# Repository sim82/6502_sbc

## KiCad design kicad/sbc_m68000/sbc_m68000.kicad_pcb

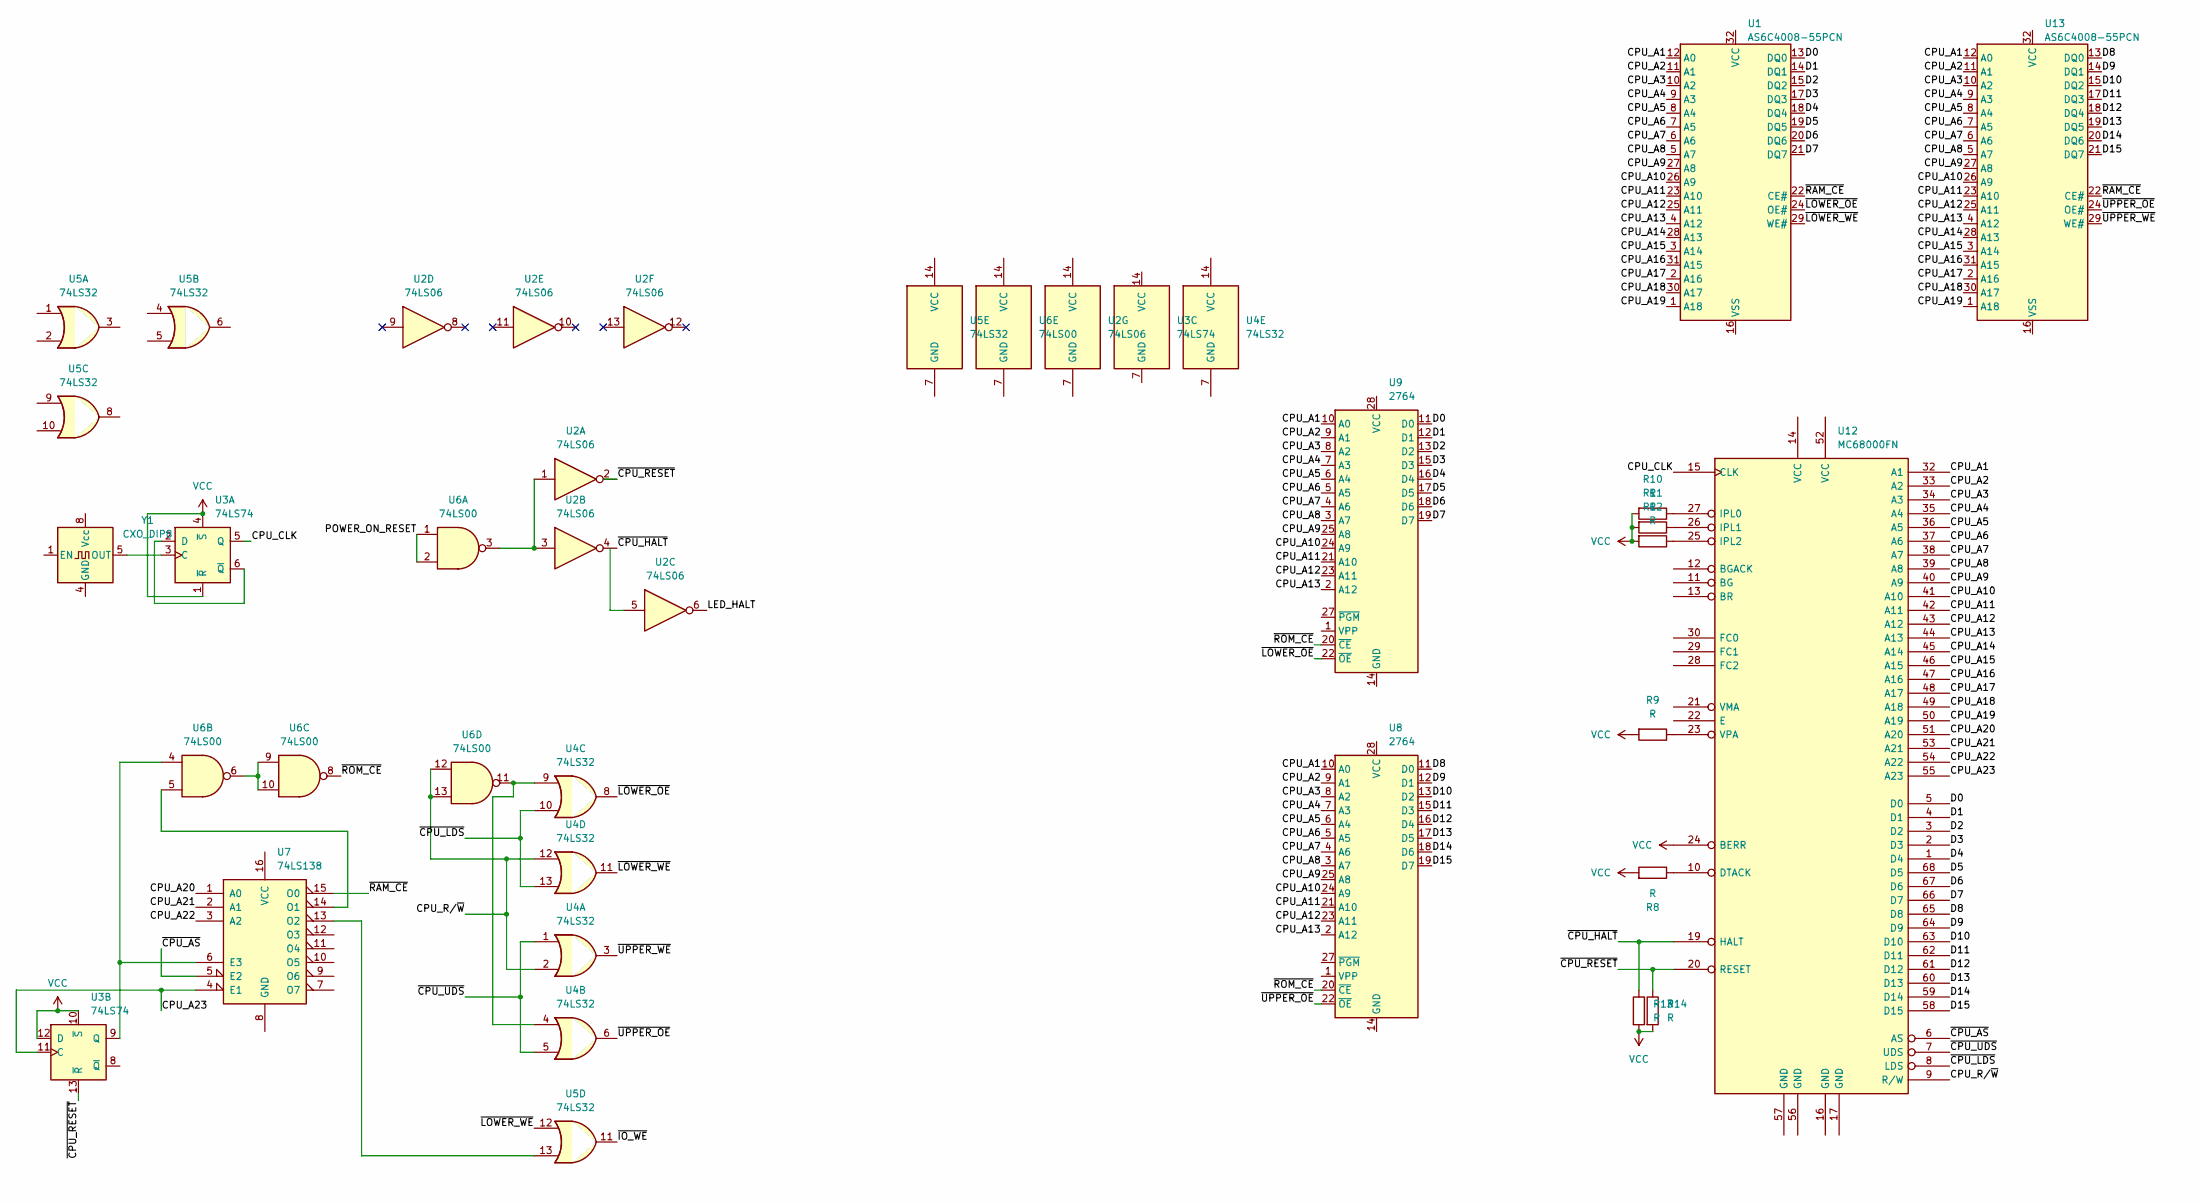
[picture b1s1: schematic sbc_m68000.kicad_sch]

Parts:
R8, R9, R10, R11, R12, R13, R14: R; R_0805_2012Metric_Pad1.20x1.40mm_HandSolder
U1, U13: AS6C4008-55PCN; TSOP-II-32_21.0x10.2mm_P1.27mm
U2: 74LS06; SO-14_3.9x8.65mm_P1.27mm
U3: 74LS74; SO-14_3.9x8.65mm_P1.27mm
U4, U5: 74LS32; SO-14_3.9x8.65mm_P1.27mm
U6: 74LS00; SO-14_3.9x8.65mm_P1.27mm
U7: 74LS138; SO-16_3.9x9.9mm_P1.27mm
U8, U9: 2764; DIP-28_W15.24mm_Socket
U12: MC68000FN; PLCC-68
Y1: CXO_DIP8; Oscillator_DIP-8

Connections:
/CPU_A1: U1.12 (A0), U8.10 (A0), U9.10 (A0), U12.32 (A1), U13.12 (A0)
/CPU_A2: U1.11 (A1), U8.9 (A1), U9.9 (A1), U12.33 (A2), U13.11 (A1)
/CPU_A3: U1.10 (A2), U8.8 (A2), U9.8 (A2), U12.34 (A3), U13.10 (A2)
/CPU_A4: U1.9 (A3), U8.7 (A3), U9.7 (A3), U12.35 (A4), U13.9 (A3)
/CPU_A5: U1.8 (A4), U8.6 (A4), U9.6 (A4), U12.36 (A5), U13.8 (A4)
/CPU_A6: U1.7 (A5), U8.5 (A5), U9.5 (A5), U12.37 (A6), U13.7 (A5)
/CPU_A7: U1.6 (A6), U8.4 (A6), U9.4 (A6), U12.38 (A7), U13.6 (A6)
/CPU_A8: U1.5 (A7), U8.3 (A7), U9.3 (A7), U12.39 (A8), U13.5 (A7)
/CPU_A9: U1.27 (A8), U8.25 (A8), U9.25 (A8), U12.40 (A9), U13.27 (A8)
/CPU_A10: U1.26 (A9), U8.24 (A9), U9.24 (A9), U12.41 (A10), U13.26 (A9)
/CPU_A11: U1.23 (A10), U8.21 (A10), U9.21 (A10), U12.42 (A11), U13.23 (A10)
/CPU_A12: U1.25 (A11), U8.23 (A11), U9.23 (A11), U12.43 (A12), U13.25 (A11)
/CPU_A13: U1.4 (A12), U8.2 (A12), U9.2 (A12), U12.44 (A13), U13.4 (A12)
/CPU_A14: U1.28 (A13), U12.45 (A14), U13.28 (A13)
/CPU_A15: U1.3 (A14), U12.46 (A15), U13.3 (A14)
/CPU_A16: U1.31 (A15), U12.47 (A16), U13.31 (A15)
/CPU_A17: U1.2 (A16), U12.48 (A17), U13.2 (A16)
/CPU_A18: U1.30 (A17), U12.49 (A18), U13.30 (A17)
/CPU_A19: U1.1 (A18), U12.50 (A19), U13.1 (A18)
/CPU_A20: U7.1 (A0), U12.51 (A20)
/CPU_A21: U7.2 (A1), U12.53 (A21)
/CPU_A22: U7.3 (A2), U12.54 (A22)
/CPU_A23: U3.11 (C), U7.4 (E1), U12.55 (A23)
/CPU_CLK: U3.5 (Q), U12.15 (CLK)
/CPU_R/~W: U4.2, U4.12, U6.12, U6.13, U12.9 (R/W)
/D0: U1.13 (DQ0), U9.11 (D0), U12.5 (D0)
/D1: U1.14 (DQ1), U9.12 (D1), U12.4 (D1)
/D2: U1.15 (DQ2), U9.13 (D2), U12.3 (D2)
/D3: U1.17 (DQ3), U9.15 (D3), U12.2 (D3)
/D4: U1.18 (DQ4), U9.16 (D4), U12.1 (D4)
/D5: U1.19 (DQ5), U9.17 (D5), U12.68 (D5)
/D6: U1.20 (DQ6), U9.18 (D6), U12.67 (D6)
/D7: U1.21 (DQ7), U9.19 (D7), U12.66 (D7)
/D8: U8.11 (D0), U12.65 (D8), U13.13 (DQ0)
/D9: U8.12 (D1), U12.64 (D9), U13.14 (DQ1)
/D10: U8.13 (D2), U12.63 (D10), U13.15 (DQ2)
/D11: U8.15 (D3), U12.62 (D11), U13.17 (DQ3)
/D12: U8.16 (D4), U12.61 (D12), U13.18 (DQ4)
/D13: U8.17 (D5), U12.60 (D13), U13.19 (DQ5)
/D14: U8.18 (D6), U12.59 (D14), U13.20 (DQ6)
/D15: U8.19 (D7), U12.58 (D15), U13.21 (DQ7)
/LED_HALT: U2.6
/POWER_ON_RESET: U6.1, U6.2
/~CPU_AS: U7.5 (E2), U12.6 (AS)
/~CPU_HALT: R13.1, U2.4, U12.19 (HALT)
/~CPU_LDS: U4.10, U4.13, U12.8 (LDS)
/~CPU_RESET: R14.1, U2.2, U3.13 (~R), U12.20 (RESET)
/~CPU_UDS: U4.1, U4.5, U12.7 (UDS)
/~IO_WE: U5.11
/~LOWER_OE: U1.24 (OE#), U4.8, U9.22 (~OE)
/~LOWER_WE: U1.29 (WE#), U4.11, U5.12
/~RAM_CE: U1.22 (CE#), U7.15 (O0), U13.22 (CE#)
/~ROM_CE: U6.8, U8.20 (~CE), U9.20 (~CE)
/~UPPER_OE: U4.6, U8.22 (~OE), U13.24 (OE#)
/~UPPER_WE: U4.3, U13.29 (WE#)
unnamed: U2.1, U2.3, U6.3
unnamed: U3.3 (C), Y1.5 (OUT)
unnamed: U3.2 (D), U3.6 (~Q)
unnamed: U3.9 (Q), U6.4, U7.6 (E3)
unnamed: U4.4, U4.9, U6.11
unnamed: U6.6, U6.9, U6.10
unnamed: U6.5, U7.14 (O1)
unnamed: U5.13, U7.13 (O2)
unnamed: R8.1, U12.10 (DTACK)
unnamed: R10.1, U12.27 (IPL0)
unnamed: R11.1, U12.26 (IPL1)
unnamed: R12.1, U12.25 (IPL2)
unnamed: R9.1, U12.23 (VPA)
VCC: R8.2, R9.2, R10.2, R11.2, R12.2, R13.2, R14.2, U3.1 (~R), U3.4 (~S), U3.10 (~S), U3.12 (D), U12.24 (BERR)

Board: 4 copper layers, 19 parts (0 on the bottom side), 67 nets, no tracks yet.

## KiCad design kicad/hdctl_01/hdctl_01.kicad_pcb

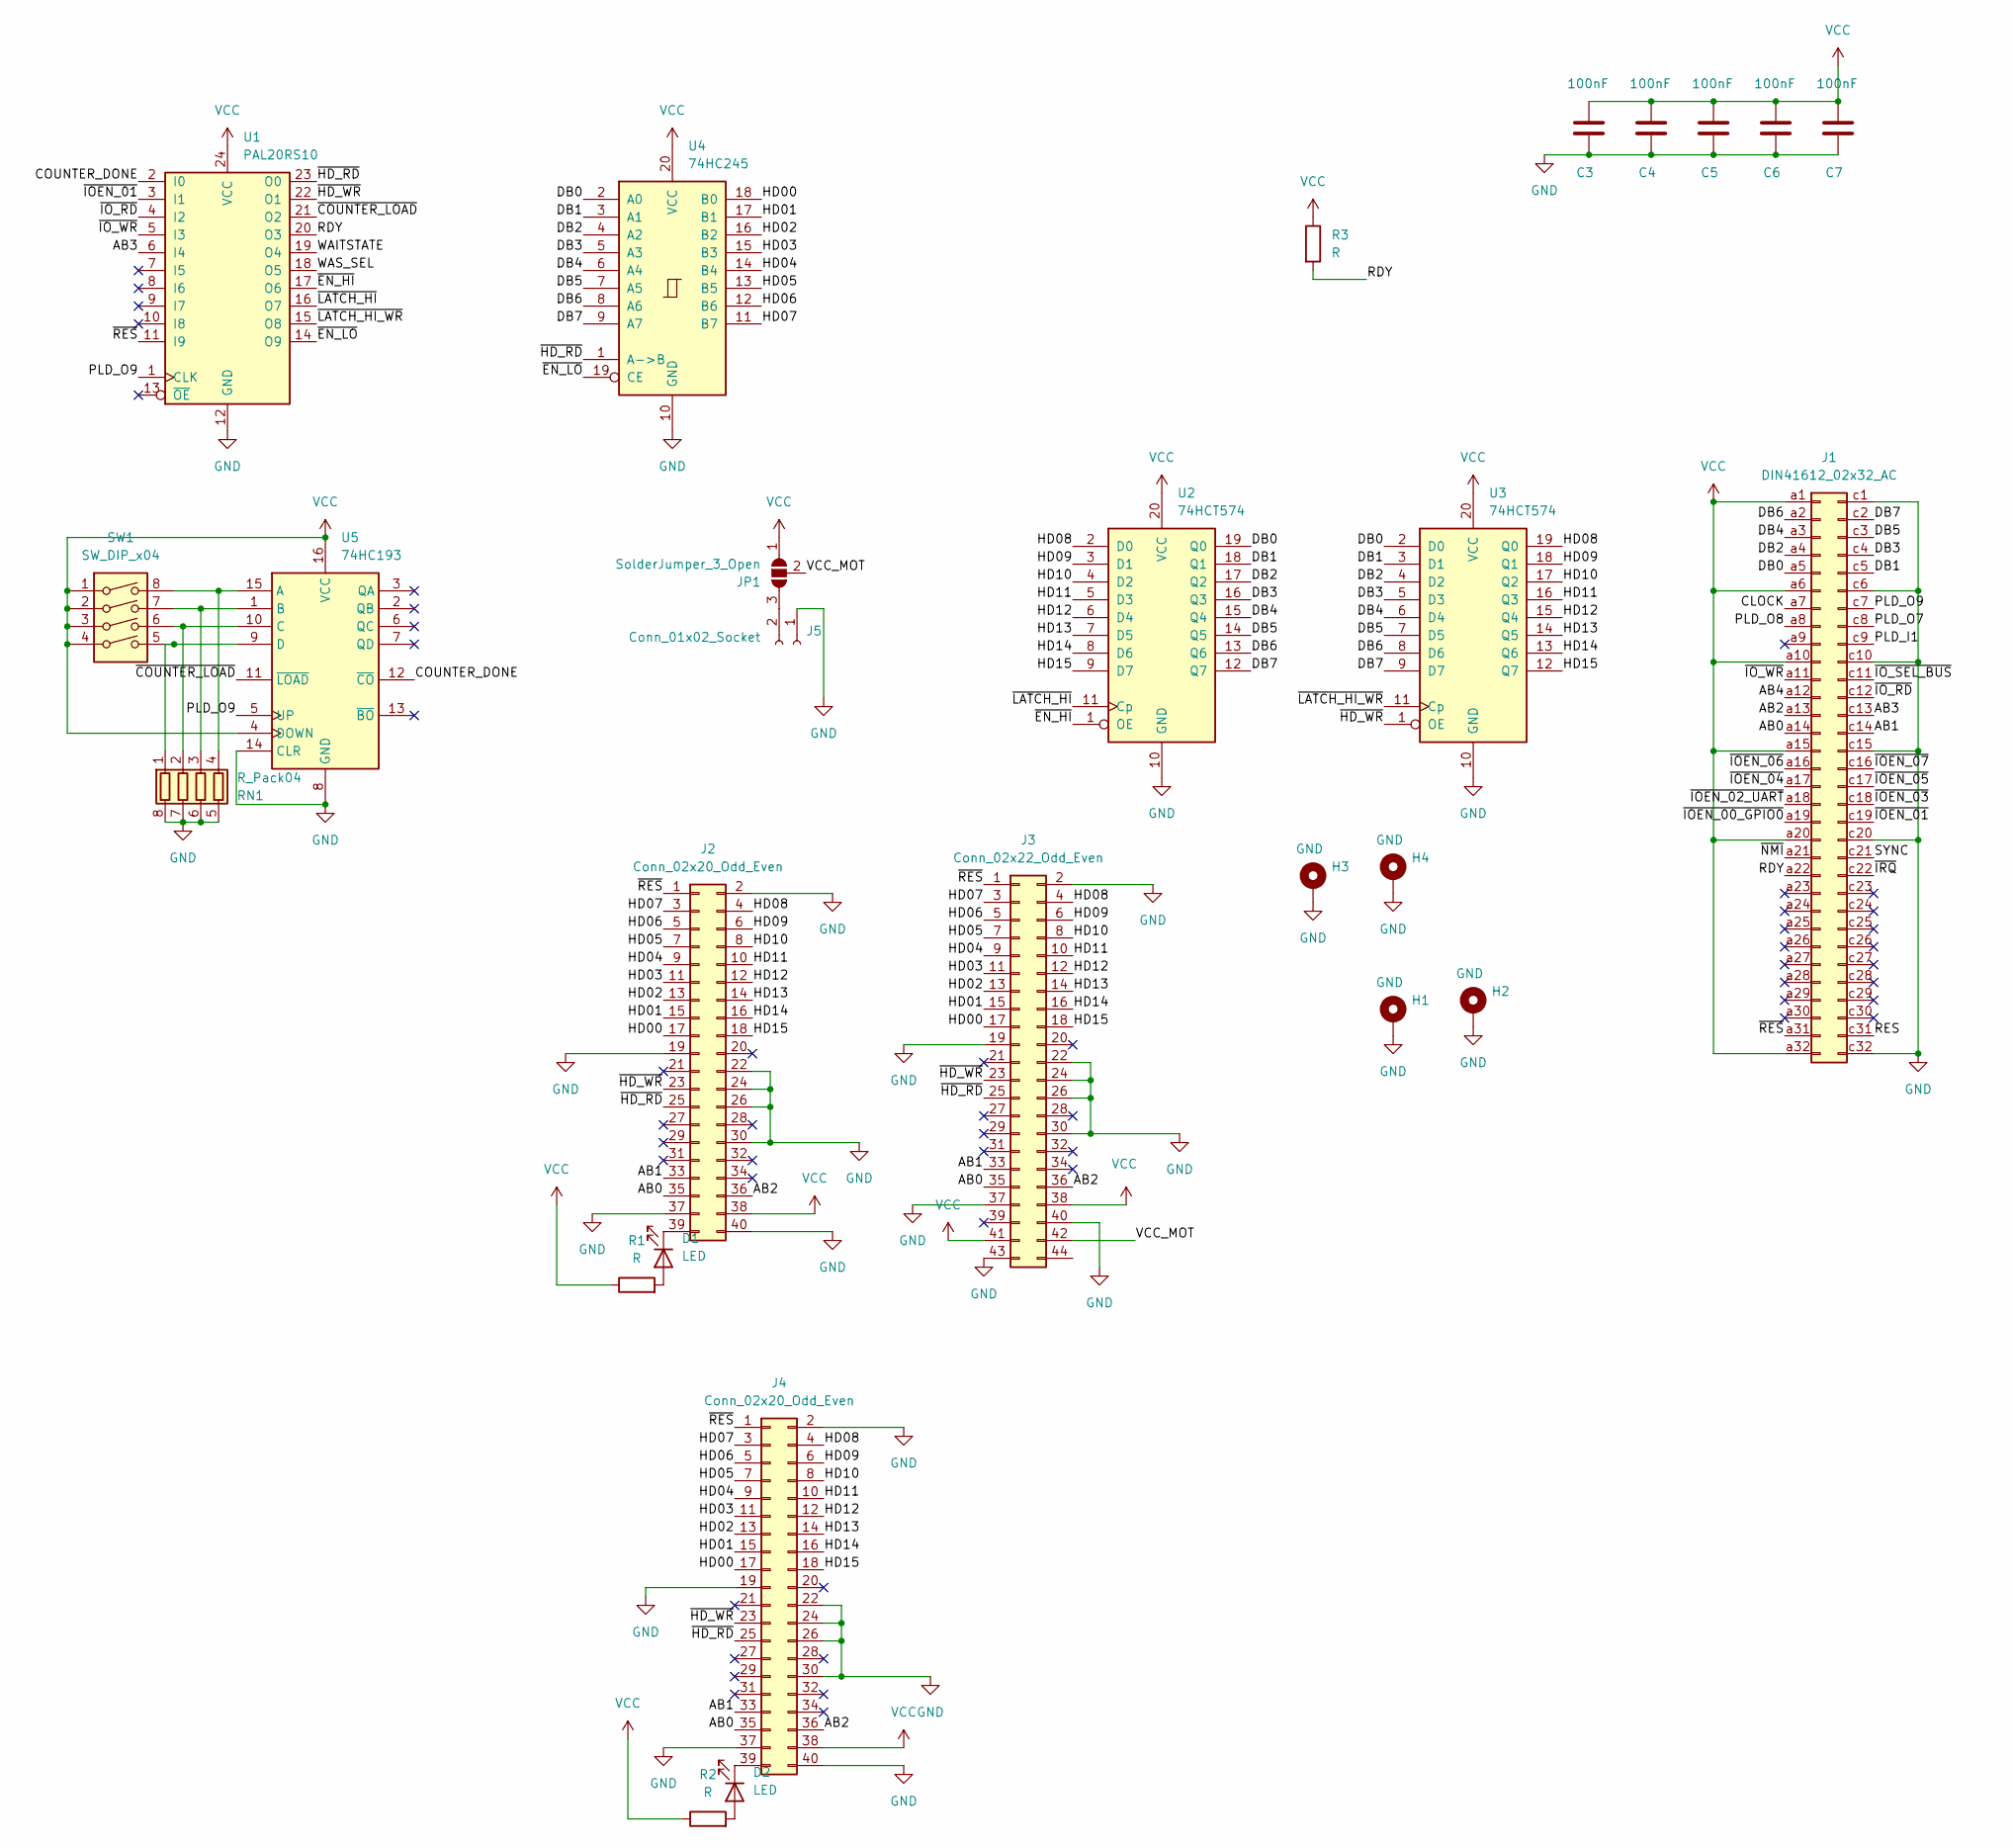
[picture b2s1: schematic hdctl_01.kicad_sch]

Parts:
C3, C4, C5, C6, C7: 100nF; C_0805_2012Metric_Pad1.18x1.45mm_HandSolder
D1, D2: LED; LED_0805_2012Metric_Pad1.15x1.40mm_HandSolder
H1, H2, H3, H4: GND; MountingHole_3.2mm_M3_DIN965_Pad
J1: DIN41612_02x32_AC; DIN41612_C_2x32_Male_Horizontal_THT
J2, J4: Conn_02x20_Odd_Even; IDC-Header_2x20_P2.54mm_Vertical
J3: Conn_02x22_Odd_Even; PinSocket_2x22_P2.00mm_Horizontal
J5: Conn_01x02_Socket; PinSocket_1x02_P2.54mm_Vertical
JP1: SolderJumper_3_Open; SolderJumper-3_P1.3mm_Open_RoundedPad1.0x1.5mm
R1, R2: R; R_0805_2012Metric_Pad1.20x1.40mm_HandSolder
R3: R; R_Axial_DIN0207_L6.3mm_D2.5mm_P7.62mm_Horizontal
RN1: R_Pack04; R_Array_Convex_4x0612
SW1: SW_DIP_x04; SW_DIP_SPSTx04_Slide_9.78x12.34mm_W8.61mm_P2.54mm
U1: PAL20RS10; DIP-24_W7.62mm_Socket
U2, U3: 74HCT574; SO-20_12.8x7.5mm_P1.27mm
U4: 74HC245; SO-20_12.8x7.5mm_P1.27mm
U5: 74HC193; SO-16_3.9x9.9mm_P1.27mm

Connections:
/AB0: J1.a14, J2.35, J3.35, J4.35
/AB1: J1.c14, J2.33, J3.33, J4.33
/AB2: J1.a13, J2.36, J3.36, J4.36
/AB3: J1.c13, U1.6 (I4)
/AB4: J1.a12
/CLOCK: J1.a7
/COUNTER_DONE: U1.2 (I0), U5.12 (~CO)
/DB0: J1.a5, U2.19 (Q0), U3.2 (D0), U4.2 (A0)
/DB1: J1.c5, U2.18 (Q1), U3.3 (D1), U4.3 (A1)
/DB2: J1.a4, U2.17 (Q2), U3.4 (D2), U4.4 (A2)
/DB3: J1.c4, U2.16 (Q3), U3.5 (D3), U4.5 (A3)
/DB4: J1.a3, U2.15 (Q4), U3.6 (D4), U4.6 (A4)
/DB5: J1.c3, U2.14 (Q5), U3.7 (D5), U4.7 (A5)
/DB6: J1.a2, U2.13 (Q6), U3.8 (D6), U4.8 (A6)
/DB7: J1.c2, U2.12 (Q7), U3.9 (D7), U4.9 (A7)
/HD00: J2.17, J3.17, J4.17, U4.18 (B0)
/HD01: J2.15, J3.15, J4.15, U4.17 (B1)
/HD02: J2.13, J3.13, J4.13, U4.16 (B2)
/HD03: J2.11, J3.11, J4.11, U4.15 (B3)
/HD04: J2.9, J3.9, J4.9, U4.14 (B4)
/HD05: J2.7, J3.7, J4.7, U4.13 (B5)
/HD06: J2.5, J3.5, J4.5, U4.12 (B6)
/HD07: J2.3, J3.3, J4.3, U4.11 (B7)
/HD08: J2.4, J3.4, J4.4, U2.2 (D0), U3.19 (Q0)
/HD09: J2.6, J3.6, J4.6, U2.3 (D1), U3.18 (Q1)
/HD10: J2.8, J3.8, J4.8, U2.4 (D2), U3.17 (Q2)
/HD11: J2.10, J3.10, J4.10, U2.5 (D3), U3.16 (Q3)
/HD12: J2.12, J3.12, J4.12, U2.6 (D4), U3.15 (Q4)
/HD13: J2.14, J3.14, J4.14, U2.7 (D5), U3.14 (Q5)
/HD14: J2.16, J3.16, J4.16, U2.8 (D6), U3.13 (Q6)
/HD15: J2.18, J3.18, J4.18, U2.9 (D7), U3.12 (Q7)
/PLD_I1: J1.c9
/PLD_O7: J1.c8
/PLD_O8: J1.a8
/PLD_O9: J1.c7, U1.1 (CLK), U5.5 (UP)
/RDY: J1.a22, R3.2, U1.20 (O3)
/RES: J1.c31
/SYNC: J1.c21
/VCC_MOT: J3.42, JP1.2 (C)
/WAITSTATE: U1.19 (O4)
/WAS_SEL: U1.18 (O5)
/~COUNTER_LOAD: U1.21 (O2), U5.11 (~LOAD)
/~EN_HI: U1.17 (O6), U2.1 (OE)
/~EN_LO: U1.14 (O9), U4.19 (CE)
/~HD_RD: J2.25, J3.25, J4.25, U1.23 (O0), U4.1 (A->B)
/~HD_WR: J2.23, J3.23, J4.23, U1.22 (O1), U3.1 (OE)
/~IOEN_00_GPIO0: J1.a19
/~IOEN_01: J1.c19, U1.3 (I1)
/~IOEN_02_UART: J1.a18
/~IOEN_03: J1.c18
/~IOEN_04: J1.a17
/~IOEN_05: J1.c17
/~IOEN_06: J1.a16
/~IOEN_07: J1.c16
/~IO_RD: J1.c12, U1.4 (I2)
/~IO_SEL_BUS: J1.c11
/~IO_WR: J1.a11, U1.5 (I3)
/~IRQ: J1.c22
/~LATCH_HI_WR: U1.15 (O8), U3.11 (Cp)
/~LATCH_HI: U1.16 (O7), U2.11 (Cp)
/~NMI: J1.a21
/~RES: J1.a31, J2.1, J3.1, J4.1, U1.11 (I9)
GND: C3.2, C4.2, C5.2, C6.2, C7.2, H1.1, H2.1, H3.1, H4.1, J1.c1, J1.c6, J1.c10, J1.c15, J1.c20, J1.c32, J2.2, J2.19, J2.22, J2.24, J2.26, J2.30, J2.37, J2.40, J3.2, J3.19, J3.22, J3.24, J3.26, J3.30, J3.37, J3.40, J3.43, J4.2, J4.19, J4.22, J4.24, J4.26, J4.30, J4.37, J4.40, J5.1, RN1.5 (R4.2), RN1.6 (R3.2), RN1.7 (R2.2), RN1.8 (R1.2), U1.12 (GND), U2.10 (GND), U3.10 (GND), U4.10 (GND), U5.8 (GND), U5.14 (CLR)
unnamed: D1.2 (A), R1.2
unnamed: D1.1 (K), J2.39
unnamed: D2.2 (A), R2.2
unnamed: D2.1 (K), J4.39
unnamed: J5.2, JP1.3 (B)
unnamed: RN1.1 (R1.1), SW1.5, U5.9 (D)
unnamed: RN1.2 (R2.1), SW1.6, U5.10 (C)
unnamed: RN1.3 (R3.1), SW1.7, U5.1 (B)
unnamed: RN1.4 (R4.1), SW1.8, U5.15 (A)
VCC: C3.1, C4.1, C5.1, C6.1, C7.1, J1.a1, J1.a6, J1.a10, J1.a15, J1.a20, J1.a32, J2.38, J3.38, J3.41, J4.38, JP1.1 (A), R1.1, R2.1, R3.1, SW1.1, SW1.2, SW1.3, SW1.4, U1.24 (VCC), U2.20 (VCC), U3.20 (VCC), U4.20 (VCC), U5.4 (DOWN), U5.16 (VCC)

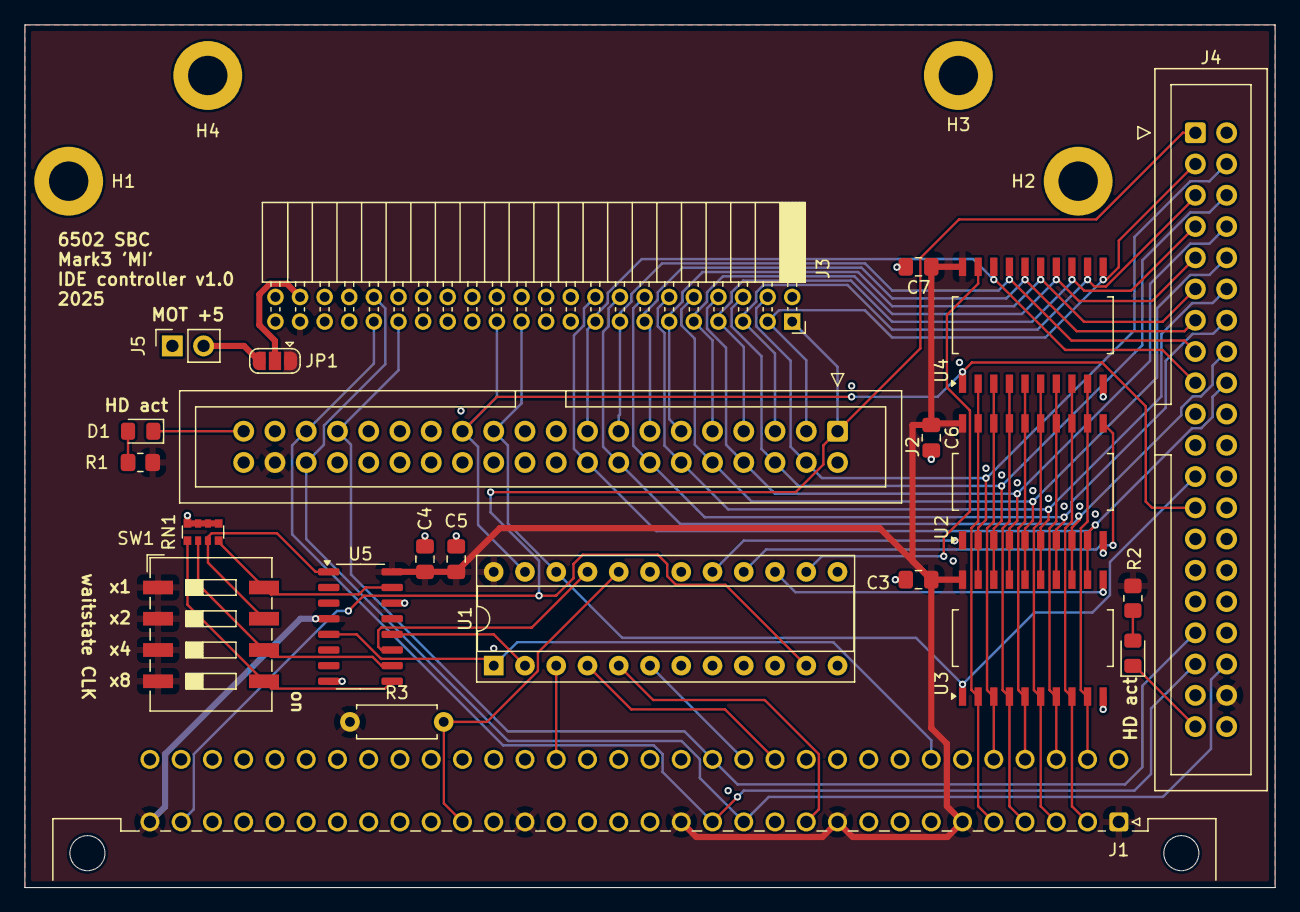
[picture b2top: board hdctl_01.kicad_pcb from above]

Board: 4 copper layers, 101.6 x 70.1 mm, 27 parts (0 on the bottom side), 54 nets.

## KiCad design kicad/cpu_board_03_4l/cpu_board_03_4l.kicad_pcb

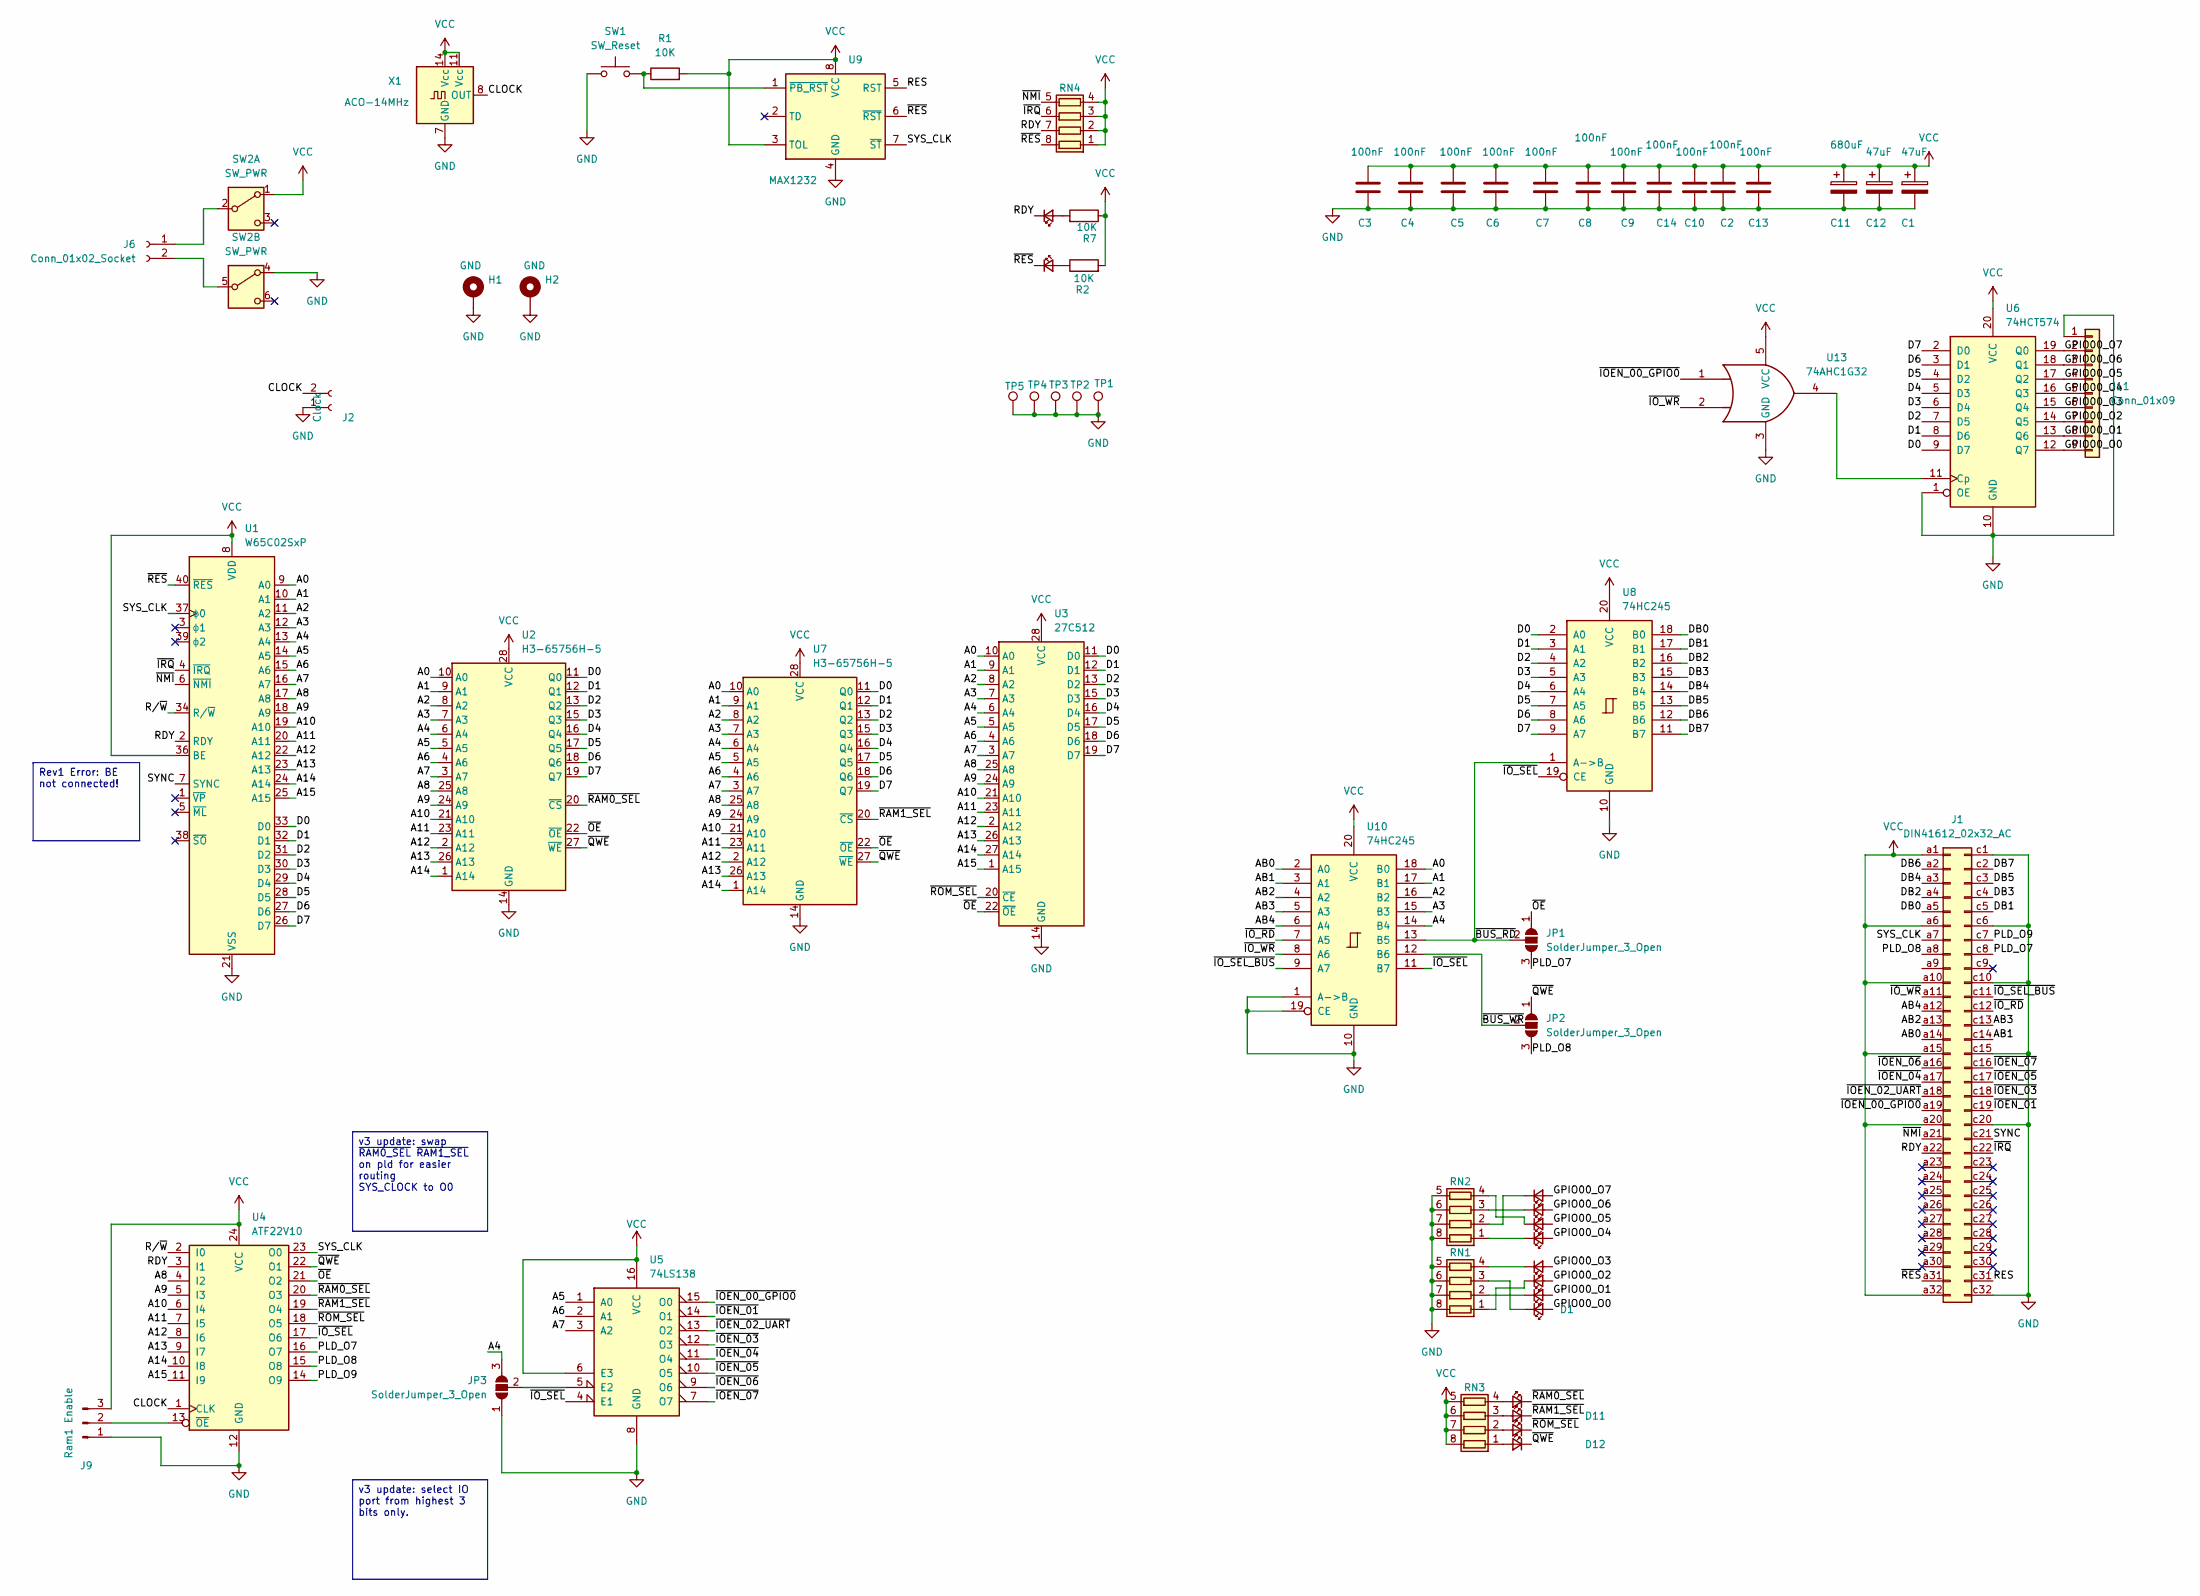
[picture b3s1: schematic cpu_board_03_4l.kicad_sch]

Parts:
C1, C12: 47uF; CP_Radial_D4.0mm_P2.00mm
C2, C3, C4, C5, C6, C7, C8, C9, C10, C13, C14: 100nF; C_0805_2012Metric_Pad1.18x1.45mm_HandSolder
C11: 680uF; CP_Radial_D8.0mm_P5.00mm
D1, D2, D3, D4, D5, D6, D7, D8, D9, D10, D11, D12, D13, D14: LED_Small; LED_0805_2012Metric_Pad1.15x1.40mm_HandSolder
H1, H2: GND; MountingHole_3.2mm_M3_DIN965_Pad
J1: DIN41612_02x32_AC; DIN41612_C_2x32_Male_Horizontal_THT
J2: Clock; PinSocket_1x02_P2.54mm_Vertical
J6: Conn_01x02_Socket; PinSocket_1x02_P2.54mm_Vertical
J9: Ram1 Enable; PinHeader_1x03_P2.54mm_Vertical
J11: Conn_01x09; PinSocket_1x09_P2.54mm_Vertical
JP1, JP2, JP3: SolderJumper_3_Open; SolderJumper-3_P1.3mm_Open_RoundedPad1.0x1.5mm
R1, R2, R7: 10K; R_0805_2012Metric_Pad1.20x1.40mm_HandSolder
RN1, RN2, RN3, RN4: R_Pack04; R_Array_Convex_4x0612
SW1: SW_Reset; SW_TH_Tactile_Omron_B3F-10xx
SW2: SW_PWR; 7x7DPDT
TP1, TP2, TP3, TP4, TP5: TestPoint; TestPoint_Loop_D1.80mm_Drill1.0mm_Beaded
U1: W65C02SxP; DIP-40_W15.24mm_Socket
U2, U7: H3-65756H-5; DIP-28_W7.62mm_Socket
U3: 27C512; DIP-28_W15.24mm_Socket
U4: ATF22V10; DIP-24_W7.62mm_Socket
U5: 74LS138; SO-16_3.9x9.9mm_P1.27mm
U6: 74HCT574; SO-20_12.8x7.5mm_P1.27mm
U8, U10: 74HC245; SO-20_12.8x7.5mm_P1.27mm
U9: MAX1232; SO-8_3.9x4.9mm_P1.27mm
U13: 74AHC1G32; SOT-23-5_HandSoldering
X1: ACO-14MHz; DIP-14_W7.62mm_Socket

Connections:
/A0: U1.9 (A0), U2.10 (A0), U3.10 (A0), U7.10 (A0), U10.18 (B0)
/A1: U1.10 (A1), U2.9 (A1), U3.9 (A1), U7.9 (A1), U10.17 (B1)
/A2: U1.11 (A2), U2.8 (A2), U3.8 (A2), U7.8 (A2), U10.16 (B2)
/A3: U1.12 (A3), U2.7 (A3), U3.7 (A3), U7.7 (A3), U10.15 (B3)
/A4: JP3.3 (B), U1.13 (A4), U2.6 (A4), U3.6 (A4), U7.6 (A4), U10.14 (B4)
/A5: U1.14 (A5), U2.5 (A5), U3.5 (A5), U5.1 (A0), U7.5 (A5)
/A6: U1.15 (A6), U2.4 (A6), U3.4 (A6), U5.2 (A1), U7.4 (A6)
/A7: U1.16 (A7), U2.3 (A7), U3.3 (A7), U5.3 (A2), U7.3 (A7)
/A8: U1.17 (A8), U2.25 (A8), U3.25 (A8), U4.4 (I2), U7.25 (A8)
/A9: U1.18 (A9), U2.24 (A9), U3.24 (A9), U4.5 (I3), U7.24 (A9)
/A10: U1.19 (A10), U2.21 (A10), U3.21 (A10), U4.6 (I4), U7.21 (A10)
/A11: U1.20 (A11), U2.23 (A11), U3.23 (A11), U4.7 (I5), U7.23 (A11)
/A12: U1.22 (A12), U2.2 (A12), U3.2 (A12), U4.8 (I6), U7.2 (A12)
/A13: U1.23 (A13), U2.26 (A13), U3.26 (A13), U4.9 (I7), U7.26 (A13)
/A14: U1.24 (A14), U2.1 (A14), U3.27 (A14), U4.10 (I8), U7.1 (A14)
/A15: U1.25 (A15), U3.1 (A15), U4.11 (I9)
/AB0: J1.a14, U10.2 (A0)
/AB1: J1.c14, U10.3 (A1)
/AB2: J1.a13, U10.4 (A2)
/AB3: J1.c13, U10.5 (A3)
/AB4: J1.a12, U10.6 (A4)
/CLOCK: J2.2, U4.1 (CLK), X1.8 (OUT)
/D0: U1.33 (D0), U2.11 (Q0), U3.11 (D0), U6.9 (D7), U7.11 (Q0), U8.2 (A0)
/D1: U1.32 (D1), U2.12 (Q1), U3.12 (D1), U6.8 (D6), U7.12 (Q1), U8.3 (A1)
/D2: U1.31 (D2), U2.13 (Q2), U3.13 (D2), U6.7 (D5), U7.13 (Q2), U8.4 (A2)
/D3: U1.30 (D3), U2.15 (Q3), U3.15 (D3), U6.6 (D4), U7.15 (Q3), U8.5 (A3)
/D4: U1.29 (D4), U2.16 (Q4), U3.16 (D4), U6.5 (D3), U7.16 (Q4), U8.6 (A4)
/D5: U1.28 (D5), U2.17 (Q5), U3.17 (D5), U6.4 (D2), U7.17 (Q5), U8.7 (A5)
/D6: U1.27 (D6), U2.18 (Q6), U3.18 (D6), U6.3 (D1), U7.18 (Q6), U8.8 (A6)
/D7: U1.26 (D7), U2.19 (Q7), U3.19 (D7), U6.2 (D0), U7.19 (Q7), U8.9 (A7)
/DB0: J1.a5, U8.18 (B0)
/DB1: J1.c5, U8.17 (B1)
/DB2: J1.a4, U8.16 (B2)
/DB3: J1.c4, U8.15 (B3)
/DB4: J1.a3, U8.14 (B4)
/DB5: J1.c3, U8.13 (B5)
/DB6: J1.a2, U8.12 (B6)
/DB7: J1.c2, U8.11 (B7)
/GPIO00_O0: D1.2 (A), J11.9, U6.12 (Q7)
/GPIO00_O1: D2.2 (A), J11.8, U6.13 (Q6)
/GPIO00_O2: D3.2 (A), J11.7, U6.14 (Q5)
/GPIO00_O3: D4.2 (A), J11.6, U6.15 (Q4)
/GPIO00_O4: D5.2 (A), J11.5, U6.16 (Q3)
/GPIO00_O5: D6.2 (A), J11.4, U6.17 (Q2)
/GPIO00_O6: D7.2 (A), J11.3, U6.18 (Q1)
/GPIO00_O7: D8.2 (A), J11.2, U6.19 (Q0)
/PLD_O7: J1.c8, JP1.3 (B), U4.16 (O7)
/PLD_O8: J1.a8, JP2.3 (B), U4.15 (O8)
/PLD_O9: J1.c7, U4.14 (O9)
/RDY: D14.1 (K), J1.a22, RN4.7 (R2.2), U1.2 (RDY), U4.3 (I1)
/RES: J1.c31, U9.5 (RST)
/R/~W: U1.34 (R/~W), U4.2 (I0)
/SYNC: J1.c21, U1.7 (SYNC)
/SYS_CLK: J1.a7, U1.37 (ϕ0), U4.23 (O0), U9.7 (~ST)
/~BUS_RD: JP1.2 (C), U8.1 (A->B), U10.13 (B5)
/~BUS_WR: JP2.2 (C), U10.12 (B6)
/~IOEN_00_GPIO0: J1.a19, U5.15 (O0), U13.1
/~IOEN_01: J1.c19, U5.14 (O1)
/~IOEN_02_UART: J1.a18, U5.13 (O2)
/~IOEN_03: J1.c18, U5.12 (O3)
/~IOEN_04: J1.a17, U5.11 (O4)
/~IOEN_05: J1.c17, U5.10 (O5)
/~IOEN_06: J1.a16, U5.9 (O6)
/~IOEN_07: J1.c16, U5.7 (O7)
/~IO_RD: J1.c12, U10.7 (A5)
/~IO_SEL_BUS: J1.c11, U10.9 (A7)
/~IO_SEL: U4.17 (O6), U5.4 (E1), U8.19 (CE), U10.11 (B7)
/~IO_WR: J1.a11, U10.8 (A6), U13.2
/~IRQ: J1.c22, RN4.6 (R3.2), U1.4 (~IRQ)
/~NMI: J1.a21, RN4.5 (R4.2), U1.6 (~NMI)
/~OE: JP1.1 (A), U2.22 (~OE), U3.22 (~OE), U4.21 (O2), U7.22 (~OE)
/~QWE: D12.1 (K), JP2.1 (A), U2.27 (~WE), U4.22 (O1), U7.27 (~WE)
/~RAM0_SEL: D10.1 (K), U2.20 (~CS), U4.20 (O3)
/~RAM1_SEL: D11.1 (K), U4.19 (O4), U7.20 (~CS)
/~RES: D13.1 (K), J1.a31, RN4.8 (R1.2), U1.40 (~RES), U9.6 (~RST)
/~ROM_SEL: D9.1 (K), U3.20 (~CE), U4.18 (O5)
GND: C1.2, C2.2, C3.2, C4.2, C5.2, C6.2, C7.2, C8.2, C9.2, C10.2, C11.2, C12.2, C13.2, C14.2, H1.1, H2.1, J1.c1, J1.c6, J1.c10, J1.c15, J1.c20, J1.c32, J2.1, J9.1, J11.1, JP3.1 (A), RN1.5 (R4.2), RN1.6 (R3.2), RN1.7 (R2.2), RN1.8 (R1.2), RN2.5 (R4.2), RN2.6 (R3.2), RN2.7 (R2.2), RN2.8 (R1.2), SW1.2, SW2.4 (A), TP1.1, TP2.1, TP3.1, TP4.1, TP5.1, U1.21 (VSS), U2.14 (GND), U3.14 (GND), U4.12 (GND), U5.8 (GND), U6.1 (OE), U6.10 (GND), U7.14 (GND), U8.10 (GND), U9.4 (GND), U10.1 (A->B), U10.10 (GND), U10.19 (CE), U13.3 (GND), X1.7 (GND)
unnamed: D1.1 (K), RN1.3 (R3.1)
unnamed: D2.1 (K), RN1.2 (R2.1)
unnamed: D3.1 (K), RN1.1 (R1.1)
unnamed: D4.1 (K), RN1.4 (R4.1)
unnamed: D5.1 (K), RN2.1 (R1.1)
unnamed: D6.1 (K), RN2.4 (R4.1)
unnamed: D7.1 (K), RN2.3 (R3.1)
unnamed: D8.1 (K), RN2.2 (R2.1)
unnamed: D9.2 (A), RN3.2 (R2.1)
unnamed: D10.2 (A), RN3.4 (R4.1)
unnamed: D11.2 (A), RN3.3 (R3.1)
unnamed: D12.2 (A), RN3.1 (R1.1)
unnamed: D13.2 (A), R2.1
unnamed: D14.2 (A), R7.2
unnamed: J6.1, SW2.2 (B)
unnamed: J6.2, SW2.5 (B)
unnamed: J9.2, U4.13 (~OE)
unnamed: JP3.2 (C), U5.5 (E2)
unnamed: U6.11 (Cp), U13.4
unnamed: R1.1, SW1.1, U9.1 (~PB_RST)
VCC: C1.1, C2.1, C3.1, C4.1, C5.1, C6.1, C7.1, C8.1, C9.1, C10.1, C11.1, C12.1, C13.1, C14.1, J1.a1, J1.a6, J1.a10, J1.a15, J1.a20, J1.a32, J9.3, R1.2, R2.2, R7.1, RN3.5 (R4.2), RN3.6 (R3.2), RN3.7 (R2.2), RN3.8 (R1.2), RN4.1 (R1.1), RN4.2 (R2.1), RN4.3 (R3.1), RN4.4 (R4.1), SW2.1 (A), U1.8 (VDD), U1.36 (BE), U2.28 (VCC), U3.28 (VCC), U4.24 (VCC), U5.6 (E3), U5.16 (VCC), U6.20 (VCC), U7.28 (VCC), U8.20 (VCC), U9.3 (TOL), U9.8 (VCC), U10.20 (VCC), U13.5 (VCC), X1.11 (Vcc), X1.14 (Vcc)

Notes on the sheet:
Rev1 Error: BE not connected!
v3 update: select IO port from highest 3 bits only.
v3 update: swap ~{RAM0_SEL} ~{RAM1_SEL} on pld for easier routing SYS_CLOCK to O0
